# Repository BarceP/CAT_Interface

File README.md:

# CAT_Interface
Radio control and audio bridge.

- Isolated digital/audio Bridge
- Usb C (2.0) connector
- Analog Gain Control
- single DB9 output connector for easy cabling.

Version 2.0:

- Due to issues it was migrated to a uC for better compatibility (in revision an STM32F072)
- Still in development

Open Hardware (CERN OHW Licence)

## TODO

- [X] Connettore Prog.
- [X] Bypass Trafo
- [X] Opt aggiungere extra opto
- [X] Silkscreen (add Group)
- [X] Zenerino + R serie su TX
- [X] Togliere RS232
- [X] Verificare BOOT0

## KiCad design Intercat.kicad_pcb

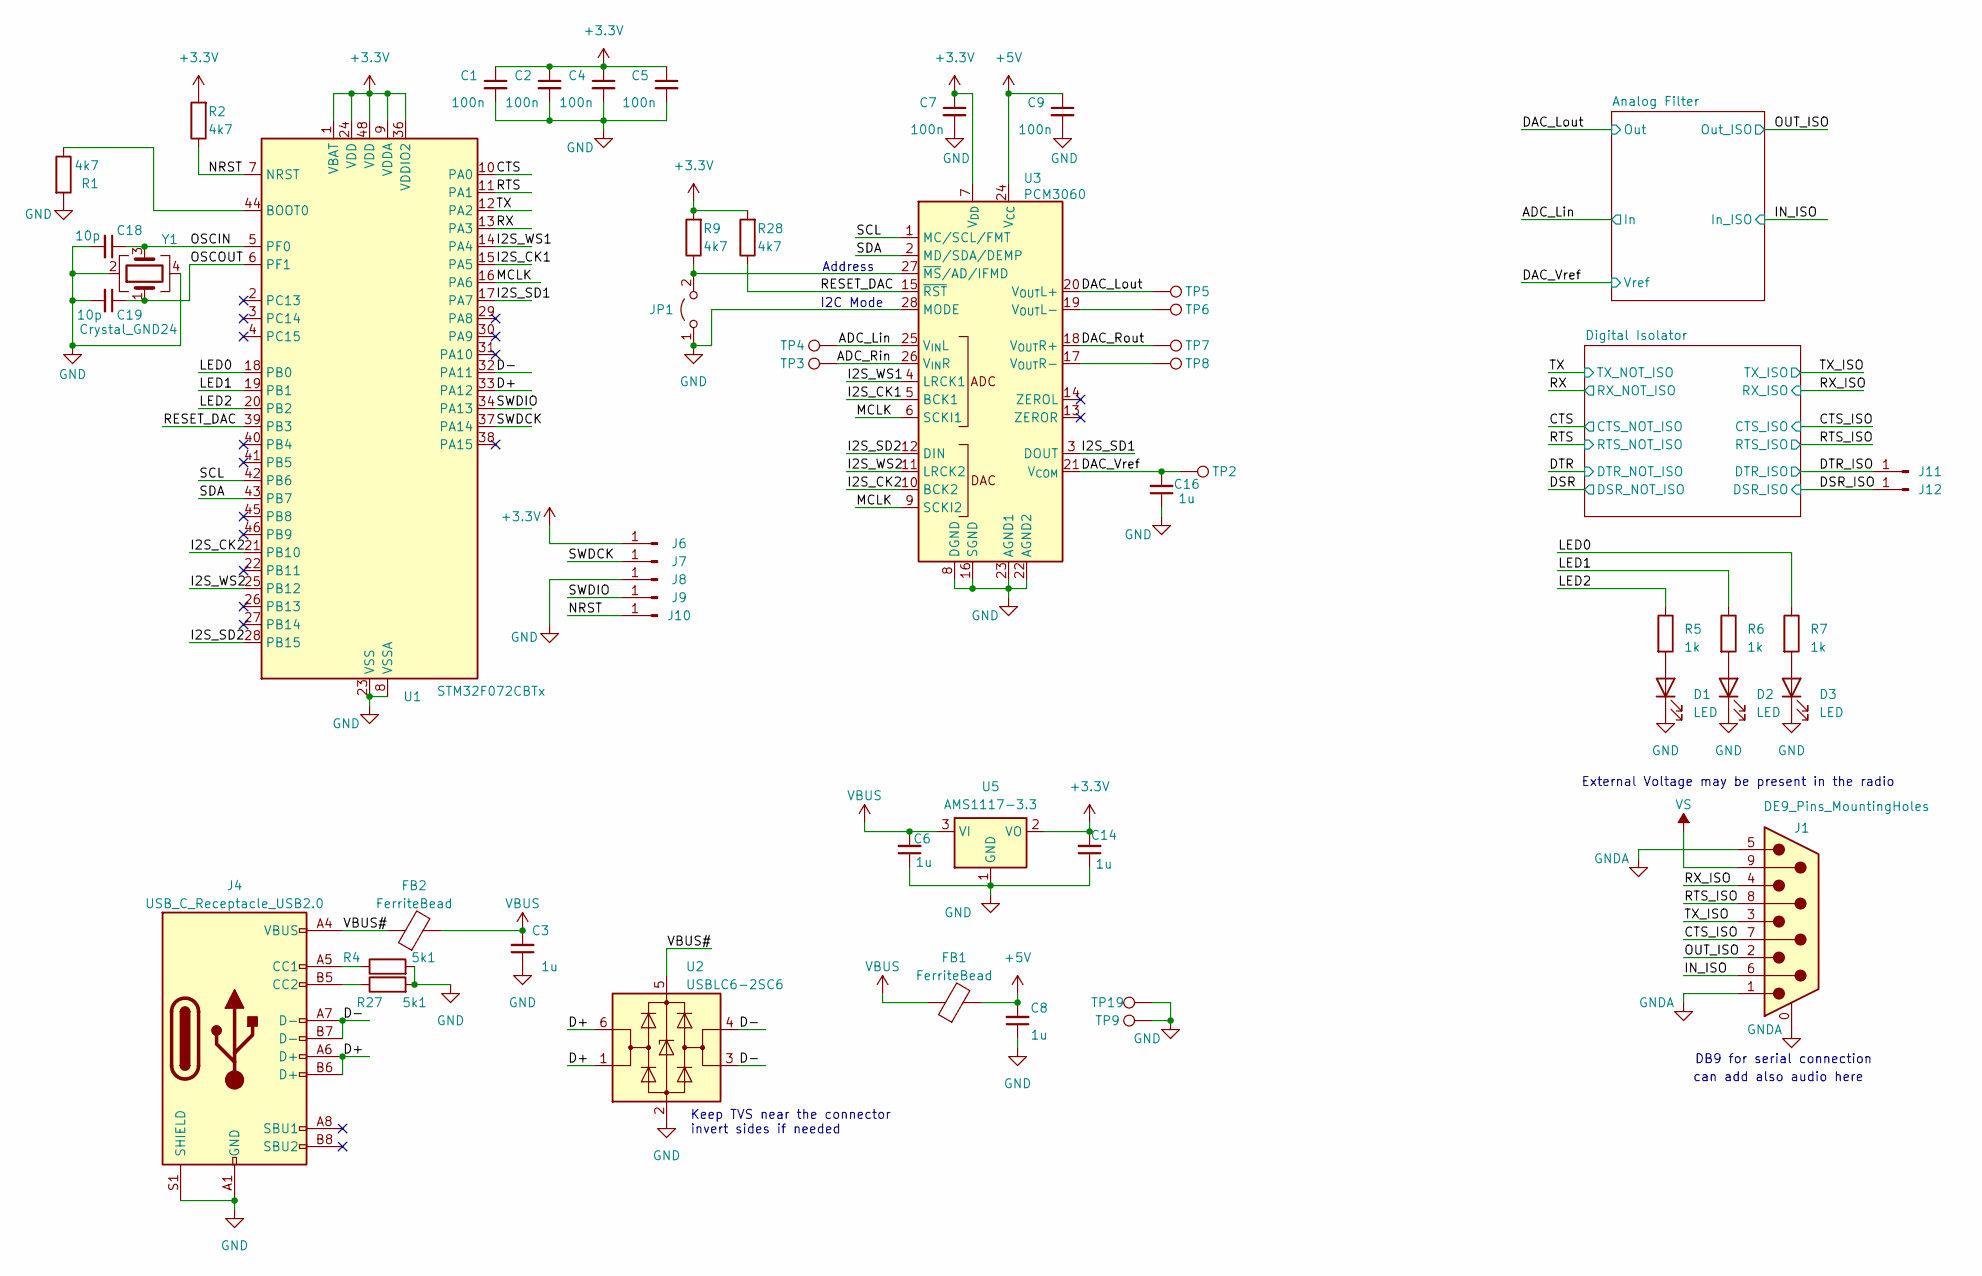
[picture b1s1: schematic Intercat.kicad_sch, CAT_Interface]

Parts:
C1, C2, C4, C5, C7, C9: 100n; C_0603_1608Metric; LCSC C14663
C3, C6, C8, C14, C16: 1u; C_0805_2012Metric; LCSC C28323
C18, C19: 10p; C_0603_1608Metric
D1, D2, D3: LED; LED_0603_1608Metric; LCSC C2286
FB1, FB2: FerriteBead; R_0603_1608Metric; LCSC C1002
J1: DE9_Pins_MountingHoles; DSUB-9_Pins_Horizontal_P2.77x2.84mm_EdgePinOffset4.94mm_Hou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
J4: USB_C_Receptacle_USB2.0; USB_C_Receptacle_GCT_USB4105-xx-A_16P_TopMnt_Horizontal; LCSC C2927038
J6, J11: Conn_01x01_Pin; SolderWirePad_1x01_SMD_1x2mm
J7, J12: SWDCLK; SolderWirePad_1x01_SMD_1x2mm
J8: GND; SolderWirePad_1x01_SMD_1x2mm
J9: SWDIO; SolderWirePad_1x01_SMD_1x2mm
J10: NRST; SolderWirePad_1x01_SMD_1x2mm
JP1: Jumper_2_Open; SolderJumper-2_P1.3mm_Open_RoundedPad1.0x1.5mm
R1, R2, R9, R28: 4k7; R_0603_1608Metric; LCSC C23162
R4, R27: 5k1; R_0603_1608Metric; LCSC C23186
R5, R6, R7: 1k; R_0603_1608Metric; LCSC C21190
TP2, TP3, TP4, TP5, TP6, TP7, TP8, TP9, TP19: TestPoint; TestPoint_Pad_D1.5mm
U1: STM32F072CBTx; LQFP-48_7x7mm_P0.5mm
U2: USBLC6-2SC6; SOT-23-6; LCSC C5261088
U3: PCM3060; TSSOP-28_4.4x9.7mm_P0.65mm
U5: AMS1117-3.3; SOT-223-3_TabPin2
Y1: Crystal_GND24; Crystal_SMD_3225-4Pin_3.2x2.5mm

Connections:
+3.3V: C1.1, C2.1, C4.1, C5.1, C7.1, C14.2, J6.1, R2.2, R9.2, R28.2, U1.1 (VBAT), U1.9 (VDDA), U1.24 (VDD), U1.36 (VDDIO2), U1.48 (VDD), U3.7 (V_{DD}), U5.2 (VO); also elsewhere on the board
+5V: C8.2, C9.1, FB1.2, U3.24 (V_{CC}); also elsewhere on the board
/ADC_Lin: TP4.1, U3.25 (V_{IN}L); also elsewhere on the board
/ADC_Rin: TP3.1, U3.26 (V_{IN}R)
/CTS: U1.10 (PA0); also elsewhere on the board
/CTS_ISO: J1.7; also elsewhere on the board
/D+: J4.A6 (D+), J4.B6 (D+), U1.33 (PA12), U2.1 (I/O1), U2.6 (I/O1)
/D-: J4.A7 (D-), J4.B7 (D-), U1.32 (PA11), U2.3 (I/O2), U2.4 (I/O2)
/DAC_Lout: TP5.1, U3.20 (V_{OUT}L+); also elsewhere on the board
/DAC_Rout: TP7.1, U3.18 (V_{OUT}R+)
/DAC_Vref: C16.2, TP2.1, U3.21 (V_{COM}); also elsewhere on the board
/DSR_ISO: J12.1; also elsewhere on the board
/DTR_ISO: J11.1; also elsewhere on the board
/I2S_CK1: U1.15 (PA5), U3.5 (BCK1)
/I2S_CK2: U1.21 (PB10), U3.10 (BCK2)
/I2S_SD1: U1.17 (PA7), U3.3 (DOUT)
/I2S_SD2: U1.28 (PB15), U3.12 (DIN)
/I2S_WS1: U1.14 (PA4), U3.4 (LRCK1)
/I2S_WS2: U1.25 (PB12), U3.11 (LRCK2)
/IN_ISO: J1.6; also elsewhere on the board
/LED0: R7.1, U1.18 (PB0)
/LED1: R6.1, U1.19 (PB1)
/LED2: R5.1, U1.20 (PB2)
/MCLK: U1.16 (PA6), U3.6 (SCKI1), U3.9 (SCKI2)
/NRST: J10.1, R2.1, U1.7 (NRST)
/OSCIN: C18.1, U1.5 (PF0), Y1.3
/OSCOUT: C19.1, U1.6 (PF1), Y1.1
/OUT_ISO: J1.2; also elsewhere on the board
/RESET_DAC: R28.1, U1.39 (PB3), U3.15 (~RST)
/RTS: U1.11 (PA1); also elsewhere on the board
/RTS_ISO: J1.8; also elsewhere on the board
/RX: U1.13 (PA3); also elsewhere on the board
/RX_ISO: J1.4; also elsewhere on the board
/SCL: U1.42 (PB6), U3.1 (MC/SCL/FMT)
/SDA: U1.43 (PB7), U3.2 (MD/SDA/DEMP)
/SWDCK: J7.1, U1.37 (PA14)
/SWDIO: J9.1, U1.34 (PA13)
/TX: U1.12 (PA2); also elsewhere on the board
/TX_ISO: J1.3; also elsewhere on the board
/VBUS#: FB2.1, J4.A4 (VBUS), J4.A9 (VBUS), J4.B4 (VBUS), J4.B9 (VBUS), U2.5 (VBUS)
GND: C1.2, C2.2, C3.1, C4.2, C5.2, C6.1, C7.2, C8.1, C9.2, C14.1, C16.1, C18.2, C19.2, D1.1 (K), D2.1 (K), D3.1 (K), J4.A1 (GND), J4.A12 (GND), J4.B1 (GND), J4.B12 (GND), J4.S1 (SHIELD), J8.1, JP1.1 (A), R1.2, R4.2, R27.2, TP9.1, TP19.1, U1.8 (VSSA), U1.23 (VSS), U1.35 (VSS), U1.47 (VSS), U2.2 (GND), U3.8 (DGND), U3.16 (SGND), U3.22 (AGND2), U3.23 (AGND1), U3.28 (MODE), U5.1 (GND), Y1.2, Y1.4; also elsewhere on the board
GNDA: J1.0 (PAD), J1.1, J1.5; also elsewhere on the board
unnamed: D1.2 (A), R5.2
unnamed: D2.2 (A), R6.2
unnamed: D3.2 (A), R7.2
unnamed: J4.A5 (CC1), R4.1
unnamed: J4.B5 (CC2), R27.1
unnamed: JP1.2 (B), R9.1, U3.27 (~MS/AD/IFMD)
unnamed: R1.1, U1.44 (BOOT0)
unnamed: TP6.1, U3.19 (V_{OUT}L-)
unnamed: TP8.1, U3.17 (V_{OUT}R-)
VBUS: C3.2, C6.2, FB1.1, FB2.2, U5.3 (VI)
VS: J1.9; also elsewhere on the board

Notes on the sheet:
can add also audio here
Address
External Voltage may be present in the radio
I2C Mode
DB9 for serial connection
Keep TVS near the connector invert sides if needed

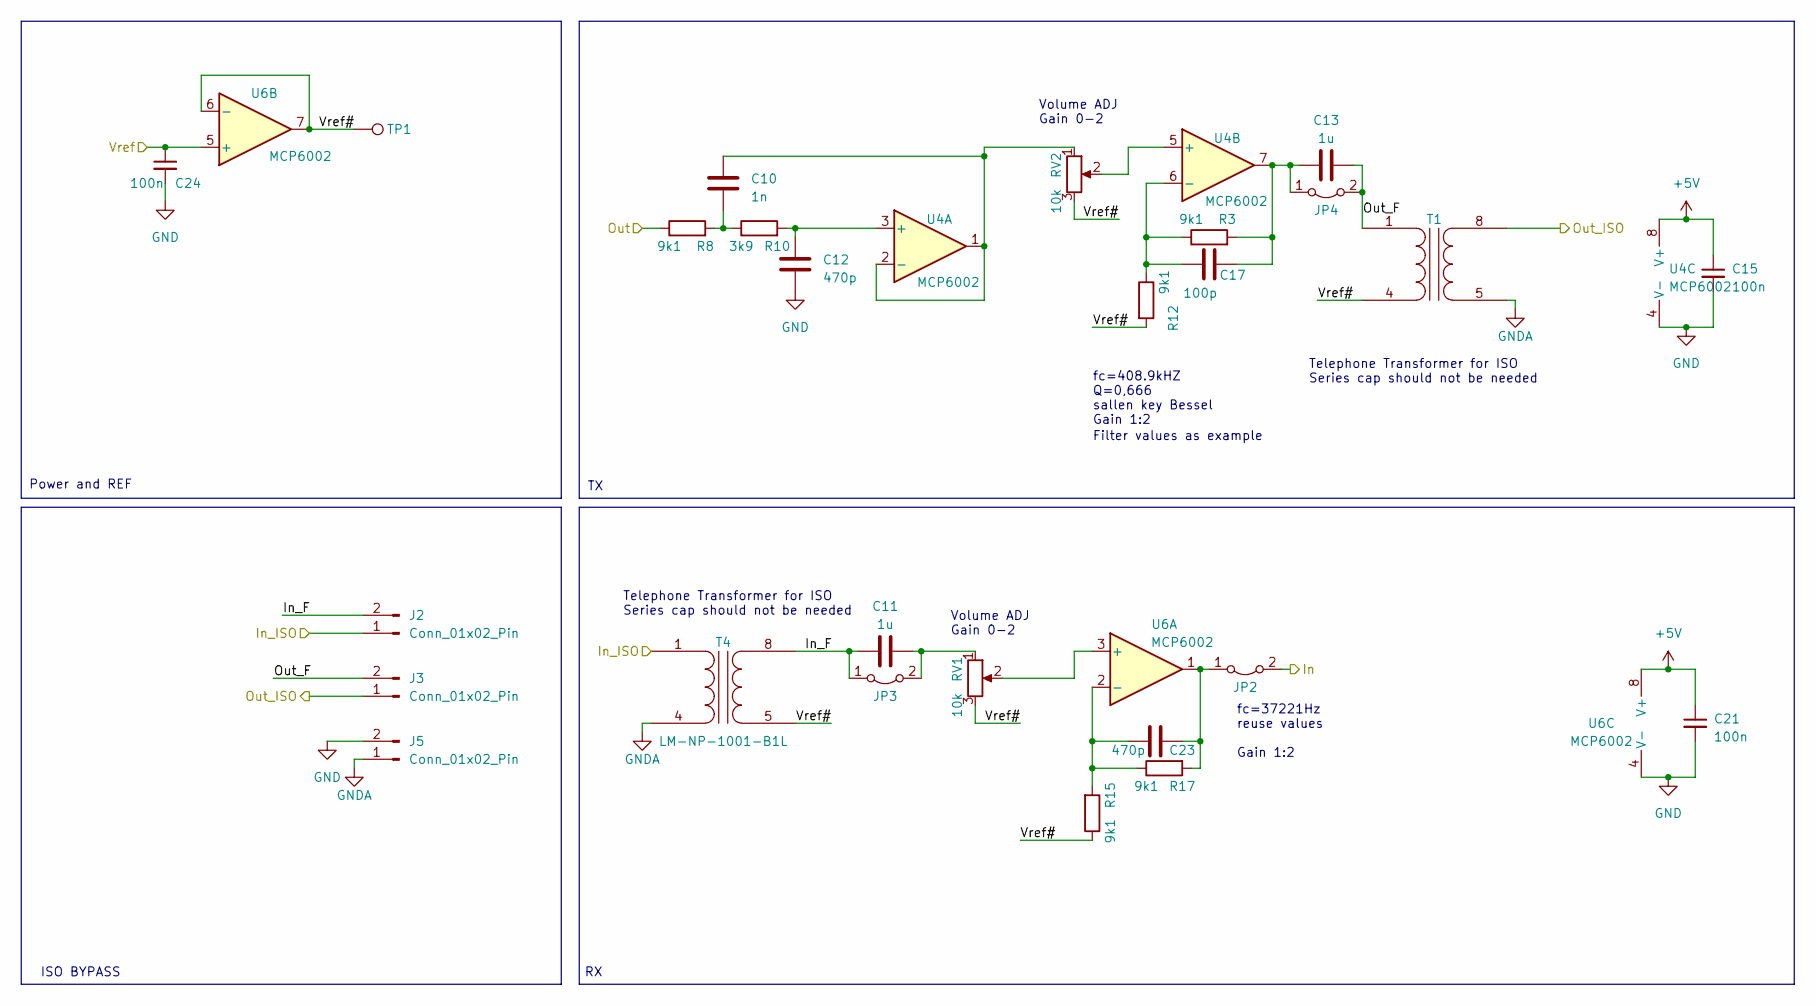
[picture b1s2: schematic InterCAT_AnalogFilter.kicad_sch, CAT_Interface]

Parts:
C10: 1n; C_0603_1608Metric
C11, C13: 1u; C_0805_2012Metric; LCSC C28323
C12, C23: 470p; C_0603_1608Metric; LCSC C1620
C15, C21, C24: 100n; C_0603_1608Metric; LCSC C14663
C17: 100p; C_0603_1608Metric
J2, J3, J5: Conn_01x02_Pin; PinHeader_1x02_P2.54mm_Vertical
JP2, JP3, JP4: Jumper_2_Bridged; SolderJumper-2_P1.3mm_Bridged_RoundedPad1.0x1.5mm
R3, R8, R12, R15, R17: 9k1; R_0603_1608Metric; LCSC C23260
R10: 3k9; R_0603_1608Metric; LCSC C23018
RV1, RV2: 10k; Potentiometer_Bourns_3386P_Vertical
T1, T4: LM-NP-1001-B1L; LCSC C5361839
TP1: TestPoint; TestPoint_Pad_D1.5mm
U4, U6: MCP6002; SOIC-8_3.9x4.9mm_P1.27mm; LCSC C7377

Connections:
+5V: C15.1, C21.1, U4.8 (V+), U6.8 (V+); also elsewhere on the board
/ADC_Lin: JP2.2 (B); also elsewhere on the board
/Analog Filter/In_F: C11.1, J2.2, JP3.1 (A), T4.8 (SB)
/Analog Filter/Out_F: C13.2, J3.2, JP4.2 (B), T1.1 (AA)
/Analog Filter/Vref#: R12.2, R15.1, RV1.3, RV2.3, T1.4 (AB), T4.5 (SA), TP1.1, U6.6 (-), U6.7
/DAC_Lout: R8.1; also elsewhere on the board
/DAC_Vref: C24.1, U6.5 (+); also elsewhere on the board
/IN_ISO: J2.1, T4.1 (AA); also elsewhere on the board
/OUT_ISO: J3.1, T1.8 (SB); also elsewhere on the board
GND: C12.2, C15.2, C21.2, C24.2, J5.2, U4.4 (V-), U6.4 (V-); also elsewhere on the board
GNDA: J5.1, T1.5 (SA), T4.4 (AB); also elsewhere on the board
unnamed: C10.2, R8.2, R10.1
unnamed: C23.2, JP2.1 (A), R17.2, U6.1
unnamed: C11.2, JP3.2 (B), RV1.1
unnamed: C13.1, C17.2, JP4.1 (A), R3.2, U4.7
unnamed: C12.1, R10.2, U4.3 (+)
unnamed: C10.1, RV2.1, U4.1, U4.2 (-)
unnamed: RV2.2, U4.5 (+)
unnamed: C17.1, R3.1, R12.1, U4.6 (-)
unnamed: RV1.2, U6.3 (+)
unnamed: C23.1, R15.2, R17.1, U6.2 (-)

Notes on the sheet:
Power and REF
fc=37221Hz reuse values Gain 1:2
Telephone Transformer for ISO Series cap should not be needed
Filter values as example
Volume ADJ Gain 0-2
fc=408.9kHZ Q=0,666 sallen key Bessel Gain 1:2
ISO BYPASS

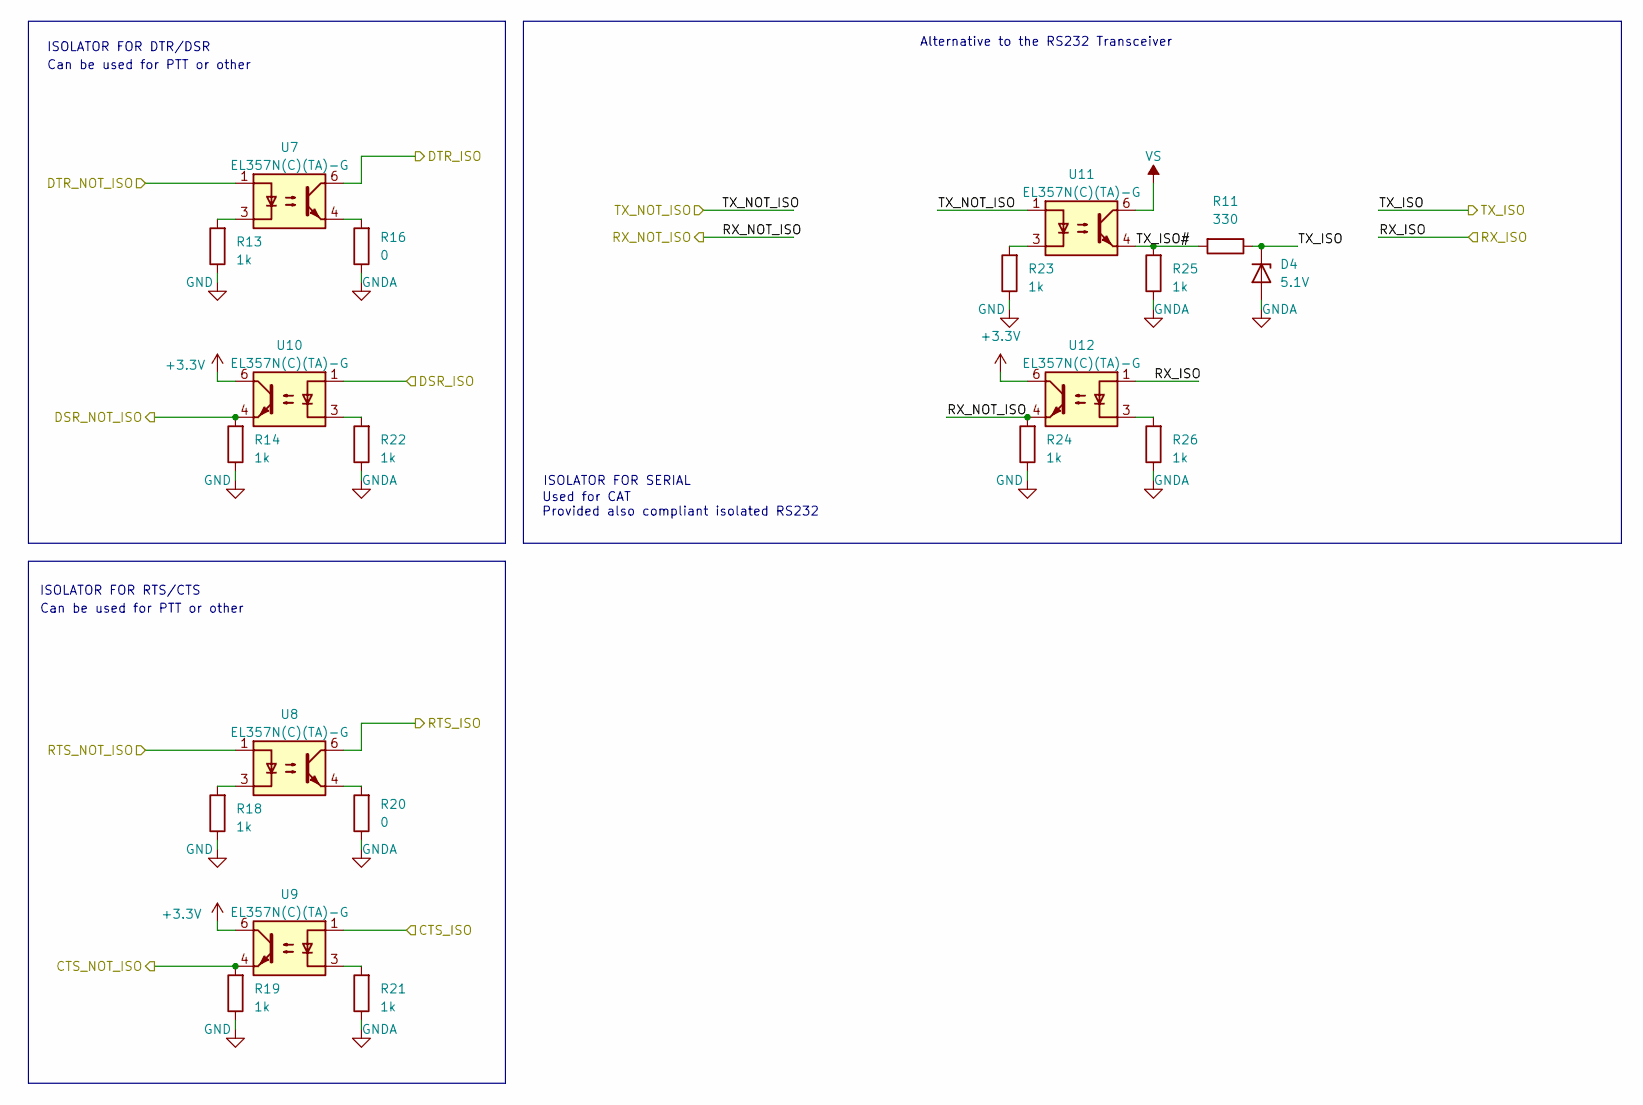
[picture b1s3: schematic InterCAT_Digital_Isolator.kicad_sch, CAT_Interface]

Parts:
D4: 5.1V; D_0603_1608Metric
R11: 330; R_0603_1608Metric
R13, R14, R18, R19, R21, R22, R23, R24, R25, R26: 1k; R_0603_1608Metric; LCSC C21190
R16, R20: 0; R_0603_1608Metric
U7, U8, U9, U10, U11, U12: EL357N(C)(TA)-G; SO-6-4_4.4x3.9mm_P2.54mm; LCSC C29981

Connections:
+3.3V: U9.6, U10.6, U12.6; also elsewhere on the board
/CTS: R19.2, U9.4; also elsewhere on the board
/CTS_ISO: U9.1; also elsewhere on the board
/DSR: R14.2, U10.4
/DSR_ISO: U10.1; also elsewhere on the board
/DTR: U7.1
/DTR_ISO: U7.6; also elsewhere on the board
/Digital Isolator/TX_ISO#: R11.2, R25.2, U11.4
/RTS: U8.1; also elsewhere on the board
/RTS_ISO: U8.6; also elsewhere on the board
/RX: R24.2, U12.4; also elsewhere on the board
/RX_ISO: U12.1; also elsewhere on the board
/TX: U11.1; also elsewhere on the board
/TX_ISO: D4.1 (K), R11.1; also elsewhere on the board
GND: R13.1, R14.1, R18.1, R19.1, R23.1, R24.1; also elsewhere on the board
GNDA: D4.2 (A), R16.1, R20.1, R21.1, R22.1, R25.1, R26.1; also elsewhere on the board
unnamed: R13.2, U7.3
unnamed: R16.2, U7.4
unnamed: R18.2, U8.3
unnamed: R20.2, U8.4
unnamed: R21.2, U9.3
unnamed: R22.2, U10.3
unnamed: R23.2, U11.3
unnamed: R26.2, U12.3
VS: U11.6; also elsewhere on the board

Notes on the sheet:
Can be used for PTT or other
ISOLATOR FOR DTR/DSR
ISOLATOR FOR RTS/CTS
Used for CAT Provided also compliant isolated RS232
Alternative to the RS232 Transceiver
ISOLATOR FOR SERIAL

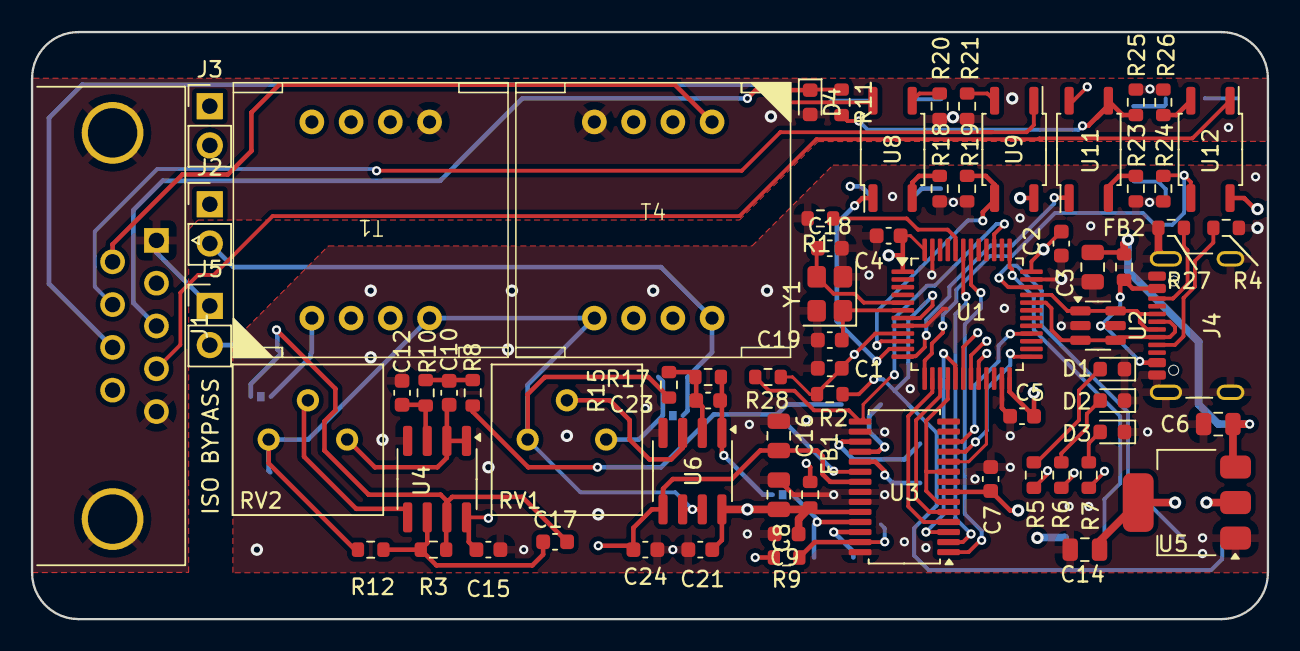
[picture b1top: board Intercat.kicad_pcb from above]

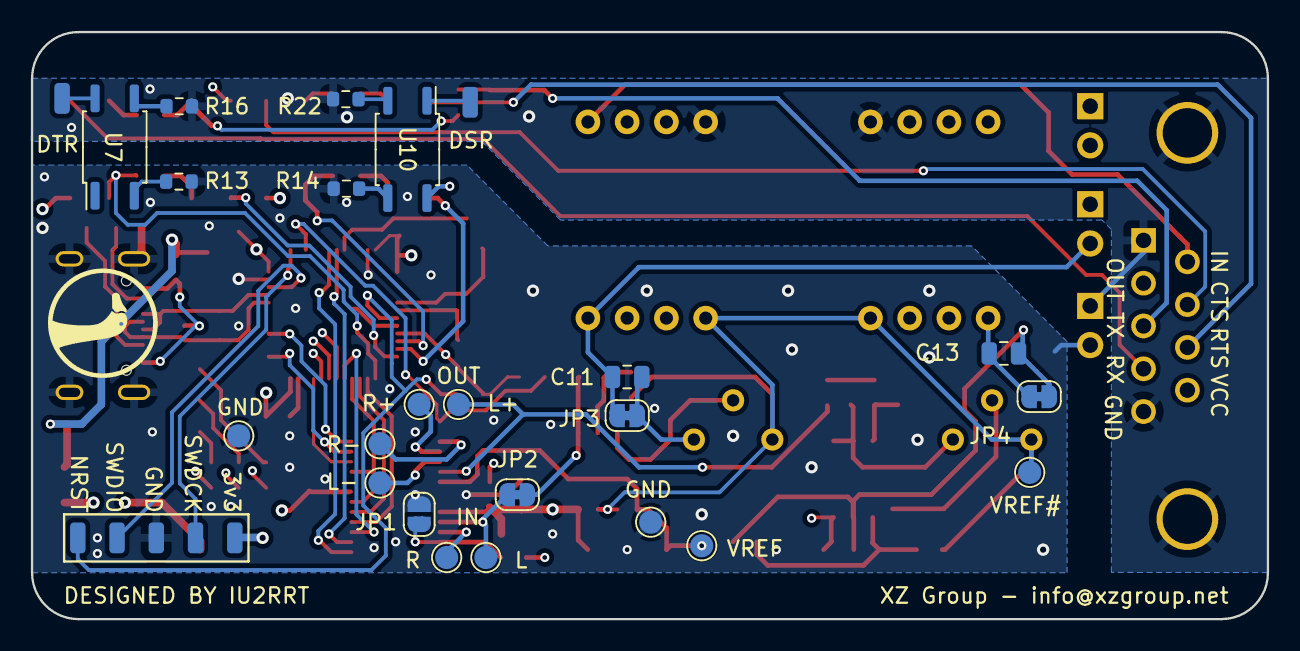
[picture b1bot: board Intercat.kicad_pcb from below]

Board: 4 copper layers, 80.0 x 38.0 mm, 99 parts (29 on the bottom side), 76 nets.

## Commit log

2023-05-27 First draft with new USB Bridge Added PCM3060 in library
2023-05-28 added PCM3060 to schematic
2023-05-28 added first draft of analog filters
2023-05-28 tracked new schematic sheet
2023-05-28 added DB9 connector
2023-05-29 added trasf. on audio I/O added MAX3250 to library
2023-05-31 first dimensioning of filters, library of MAX33251
2023-06-17 First Draft of digital isolation part Modified MAX3250 Symbol Added sheet for digital isolation
2023-06-17 changed analog filters, added gain
2023-06-18 added LEDs, small changes
2023-07-07 Started working on the PCB. alignement in analog channels. changed opamps ot Microchip RRIO basic on LCSC updated footprint on maxim Added LCSC parameter corrected some errors in GND/AGND corrected s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
2023-07-15 Corrected audio Jacks
2023-07-15 Corrected hidden errors in power nets naming
2023-07-15 added footprints for trimmers and trasf
2023-07-15 corrected footprint AND symbol of trasf
2023-07-15 first PCB placement Draft
2023-07-15 removed jack connectors, added testpoints on DAC
2023-07-17 updated hole size on transformer pcb
2023-07-22 changed optocouplers, started compiling BOM
2023-07-22 continuation on BOM
2023-07-22 added FB2 and continued with BOM
2023-07-22 completed JLC BOM and changed DB9
2023-07-22 added edge cuts, smaller PCB, bugfix
2023-07-24 changed 3d model of the transformer
2023-07-24 changed schematic to full mono
2023-07-24 reduced PCB size, started routing
2023-07-25 redone layout, reduced size, added clearance for box
2023-07-25 redone analog channels to improve dynamic range, removed DC block
2023-07-25 removed missed cap,reviewed layout
2023-07-28 corrected gain of the amplifiers and dyn range, continued PCB
2023-08-02 first PCB version
2023-08-02 reviewed silkscreen
2023-08-06 little pcb modification and silkscreen
2023-08-06 little pcb modification
2023-08-13 modified silkscreen
2023-08-13 added license and modified readme
2025-08-17 Started Version 2.0, migrated to STM32, changed some symbols, added 3V3 Supply
2025-08-17 Started work on the PBClayout of the new version
2025-08-18 First PCB version complete, to review, added 3D, changed DB9 Connecto
2025-08-18 added 3d files
2025-08-18 added trafo bypass, added zener reg, added todo
2025-08-22 added iso bypass, removed RS232, added Extra opto and prog connector
2025-10-18 added DAC_RESET and routed
